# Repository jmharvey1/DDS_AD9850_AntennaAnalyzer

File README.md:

# DDS_AD9850_AntennaAnalyzer
This is a no frills DIY Analyzer intended for frequencies ranging from 1.6 to 30 Mhz
See http://youtu.be/C6YxD72sX_Y for a description of this project

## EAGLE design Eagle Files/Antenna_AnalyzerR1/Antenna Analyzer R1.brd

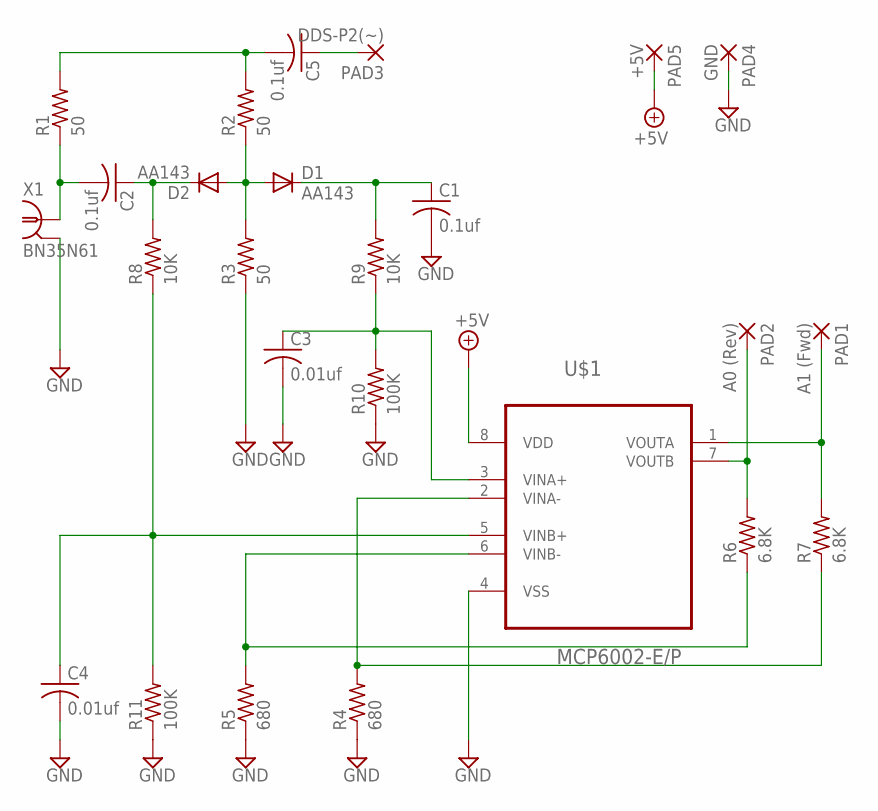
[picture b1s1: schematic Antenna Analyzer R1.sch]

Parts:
C1, C2, C5: 0.1uf; C050-025X075
C3, C4: 0.01uf; C050-025X075
D1, D2: AA143; DO07
PAD1: A1 (Fwd); 1,6/0,8
PAD2: A0 (Rev); 1,6/0,8
PAD3: DDS-P2(~); 1,6/0,8
PAD4: GND; 1,6/0,8
PAD5: +5V; 1,6/0,8
R1, R2, R3: 50; 0309/12
R4, R5: 680; 0309/12
R6, R7: 6.8K; 0309/12
R8, R9: 10K; 0309/12
R10, R11: 100K; 0309/12
U$1: MCP6002-E/P; DIP254P762X533-8
X1: BN35N61; B35N61

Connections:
+5V: PAD5.1, U$1.8 (VDD)
GND: C1.2, C3.2, C4.2, PAD4.1, R3.1, R4.1, R5.1, R10.1, R11.1, U$1.4 (VSS), X1.2, X1.3 (2), X1.4 (2), X1.5 (2)
unnamed: D1.A, D2.A, R2.1, R3.2
unnamed: C2.2, R1.1, X1.1
unnamed: C2.1, D2.C, R8.2
unnamed: C1.1, D1.C, R9.2
unnamed: C3.1, R9.1, R10.2, U$1.3 (VINA+)
unnamed: C5.2, R1.2, R2.2
unnamed: PAD2.1, R6.2, U$1.7 (VOUTB)
unnamed: PAD1.1, R7.2, U$1.1 (VOUTA)
unnamed: R5.2, R6.1, U$1.6 (VINB-)
unnamed: C4.1, R8.1, R11.2, U$1.5 (VINB+)
unnamed: R4.2, R7.1, U$1.2 (VINA-)
unnamed: C5.1, PAD3.1

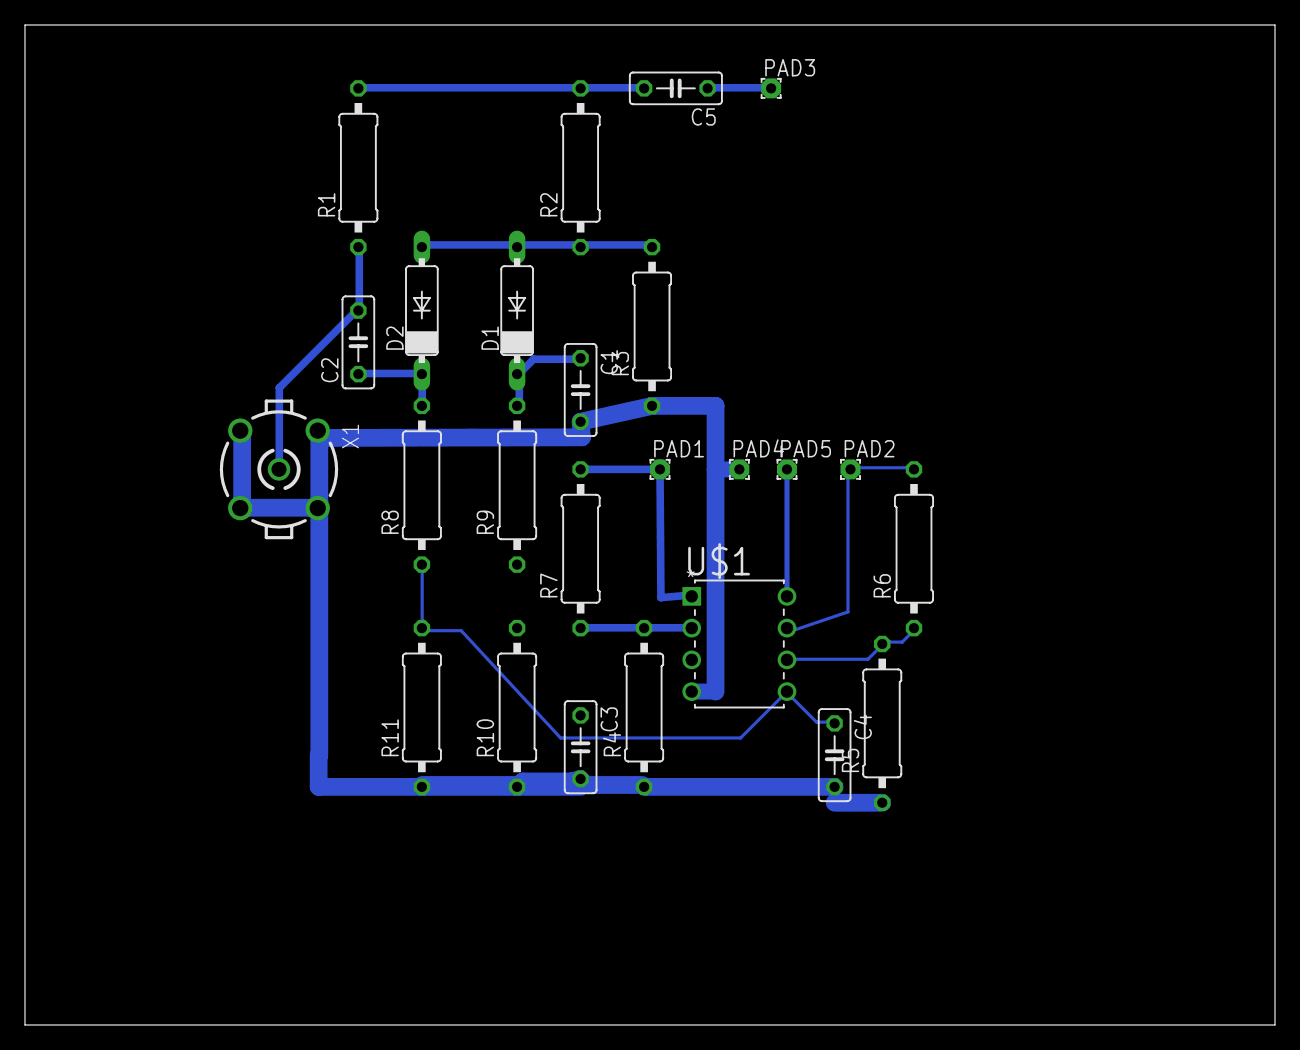
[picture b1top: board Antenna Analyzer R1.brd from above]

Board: 2 copper layers, 100.0 x 80.0 mm, 25 parts (0 on the bottom side), 14 nets.

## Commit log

2015-08-03 This is the initial entry for this respository
2015-08-12 Added code to simplify band scan choice to 128x64 sketch.
2015-09-13 Added 3rd Sketch that supports the addition of a KY040 Rotory Switch to select the Band sweep
2015-10-14 Added code to detect which Arduino board is in play (Uno/Leonardo) at compile time and select the appropriate interrupt vector. Also tweaked ISR routine in an attempt to further reduce the effects en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
2016-04-11 Added Arduino sketch pskmeter an windows application pskscope plus pskscope source code to DIY antenna analyzer project
2016-04-13 Added User Parameters entry screen
2016-04-13 Simplified verification of user param selection
2016-04-16 Corrected config screen soundcard picklist mapping error
2016-04-17 Added Band Id to main window/GUI
2016-04-18 Revised Power & voltage scaling computations to include simple constant carrier signal
2016-04-20 Updated both PSKmeter and PSKscope files to support Arduino's 10-bit A-to-D output. Previous releases degraded the data exchange to 8-bit data. Other minor changes were made related scaling and repor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
2020-05-16 Added Arduino to support Fixed Frequency Testing
2020-05-16 Removed Surplus PDF file
    Pdf file was not part of this project
